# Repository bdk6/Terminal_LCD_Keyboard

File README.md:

# Terminal_LCD_Keyboard
 A generic keypad and lcd terminal.

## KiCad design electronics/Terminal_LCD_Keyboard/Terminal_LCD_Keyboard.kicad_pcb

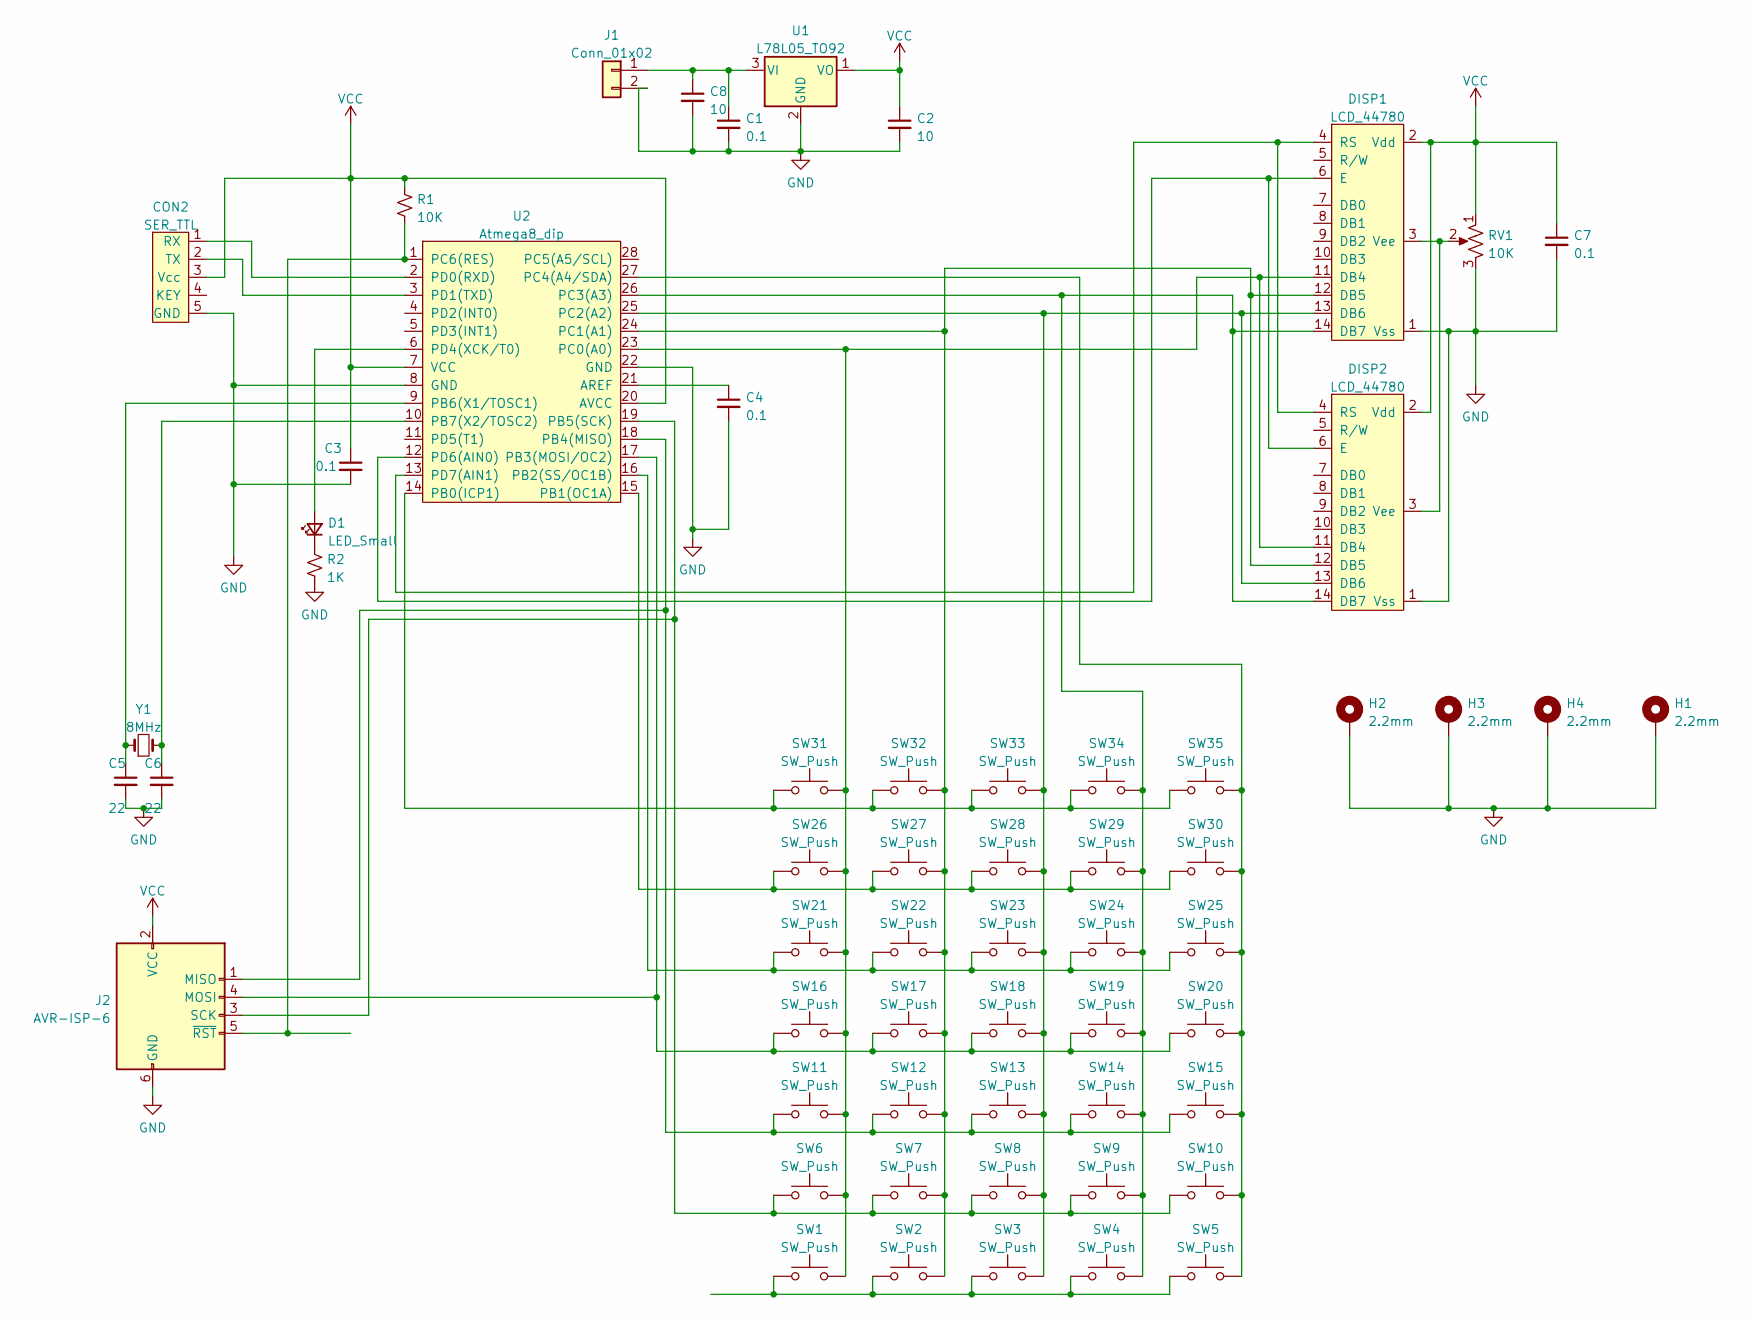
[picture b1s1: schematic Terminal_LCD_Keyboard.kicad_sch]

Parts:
C1: 0.1; C_Disc_D5.0mm_W2.5mm_P5.00mm
C2, C8: 10; CP_Radial_D6.3mm_P2.50mm
C3, C4, C7: 0.1; C_Disc_D6.0mm_W2.5mm_P5.00mm
C5, C6: 22; C_Disc_D6.0mm_W2.5mm_P5.00mm
CON2: SER_TTL; PinHeader_1x05_P2.54mm_Vertical
D1: LED_Small; D_0603_1608Metric_Pad1.05x0.95mm_HandSolder
DISP1: LCD_44780; PinHeader_1x14_P2.54mm_Vertical
DISP2: LCD_44780; PinHeader_1x16_P1.27mm_Vertical
H1, H2, H3, H4: 2.2mm; MountingHole_2.2mm_M2_DIN965_Pad
J1: Conn_01x02; PinHeader_1x02_P2.54mm_Vertical
J2: AVR-ISP-6; PinHeader_2x03_P2.54mm_Vertical
R1: 10K; R_Axial_DIN0207_L6.3mm_D2.5mm_P10.16mm_Horizontal
R2: 1K; D_0603_1608Metric_Pad1.05x0.95mm_HandSolder
RV1: 10K; Potentiometer_ACP_CA9-H5_Horizontal
SW1, SW2, SW3, SW4, SW5, SW6, SW7, SW8, SW9, SW10, SW11, SW12, SW13, SW14, SW15, SW16, SW17, SW18, SW19, SW20, SW21, SW22, SW23, SW24, SW25, SW26, SW27, SW28, SW29, SW30, SW31, SW32, SW33, SW34, SW35: SW_Push; SW_PUSH_6mm
U1: L78L05_TO92; TO-92_Inline
U2: Atmega8_dip; DIP-28_W7.62mm_Socket_LongPads
Y1: 8MHz; Crystal_HC49-U_Vertical

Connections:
GND: C1.2, C2.2, C3.2, C4.2, C5.2, C6.2, C7.2, C8.2, CON2.5 (GND), DISP1.1 (Vss), DISP2.1 (Vss), H1.1, H2.1, H3.1, H4.1, J1.2, J2.6 (GND), R2.2, RV1.3, U1.2 (GND), U2.8 (GND), U2.22 (GND)
unnamed: C1.1, C8.1, J1.1, U1.3 (VI)
unnamed: C4.1, U2.21 (AREF)
unnamed: C5.1, U2.9 (PB6(X1/TOSC1)), Y1.1
unnamed: C6.1, U2.10 (PB7(X2/TOSC2)), Y1.2
unnamed: CON2.1 (RX), U2.2 (PD0(RXD))
unnamed: CON2.2 (TX), U2.3 (PD1(TXD))
unnamed: D1.2 (A), U2.6 (PD4(XCK/T0))
unnamed: DISP1.3 (Vee), DISP2.3 (Vee), RV1.2
unnamed: DISP1.4 (RS), DISP2.4 (RS), U2.13 (PD7(AIN1))
unnamed: DISP1.6 (E), DISP2.6 (E), U2.12 (PD6(AIN0))
unnamed: DISP1.11 (DB4), DISP2.11 (DB4), SW1.2, SW6.2, SW11.2, SW16.2, SW21.2, SW26.2, SW31.2, U2.23 (PC0(A0))
unnamed: DISP1.12 (DB5), DISP2.12 (DB5), SW2.2, SW7.2, SW12.2, SW17.2, SW22.2, SW27.2, SW32.2, U2.24 (PC1(A1))
unnamed: DISP1.13 (DB6), DISP2.13 (DB6), SW3.2, SW8.2, SW13.2, SW18.2, SW23.2, SW28.2, SW33.2, U2.25 (PC2(A2))
unnamed: DISP1.14 (DB7), DISP2.14 (DB7), SW4.2, SW9.2, SW14.2, SW19.2, SW24.2, SW29.2, SW34.2, U2.26 (PC3(A3))
unnamed: J2.1 (MISO), SW11.1, SW12.1, SW13.1, SW14.1, SW15.1, U2.18 (PB4(MISO))
unnamed: J2.3 (SCK), SW6.1, SW7.1, SW8.1, SW9.1, SW10.1, U2.19 (PB5(SCK))
unnamed: J2.4 (MOSI), SW16.1, SW17.1, SW18.1, SW19.1, SW20.1, U2.17 (PB3(MOSI/OC2))
unnamed: J2.5 (~RST), R1.2, U2.1 (PC6(RES))
unnamed: D1.1 (K), R2.1
unnamed: SW1.1, SW2.1, SW3.1, SW4.1, SW5.1
unnamed: SW5.2, SW10.2, SW15.2, SW20.2, SW25.2, SW30.2, SW35.2, U2.27 (PC4(A4/SDA))
unnamed: SW21.1, SW22.1, SW23.1, SW24.1, SW25.1, U2.16 (PB2(SS/OC1B))
unnamed: SW26.1, SW27.1, SW28.1, SW29.1, SW30.1, U2.15 (PB1(OC1A))
unnamed: SW31.1, SW32.1, SW33.1, SW34.1, SW35.1, U2.14 (PB0(ICP1))
VCC: C2.1, C3.1, C7.1, CON2.3 (Vcc), DISP1.2 (Vdd), DISP2.2 (Vdd), J2.2 (VCC), R1.1, RV1.1, U1.1 (VO), U2.7 (VCC), U2.20 (AVCC)

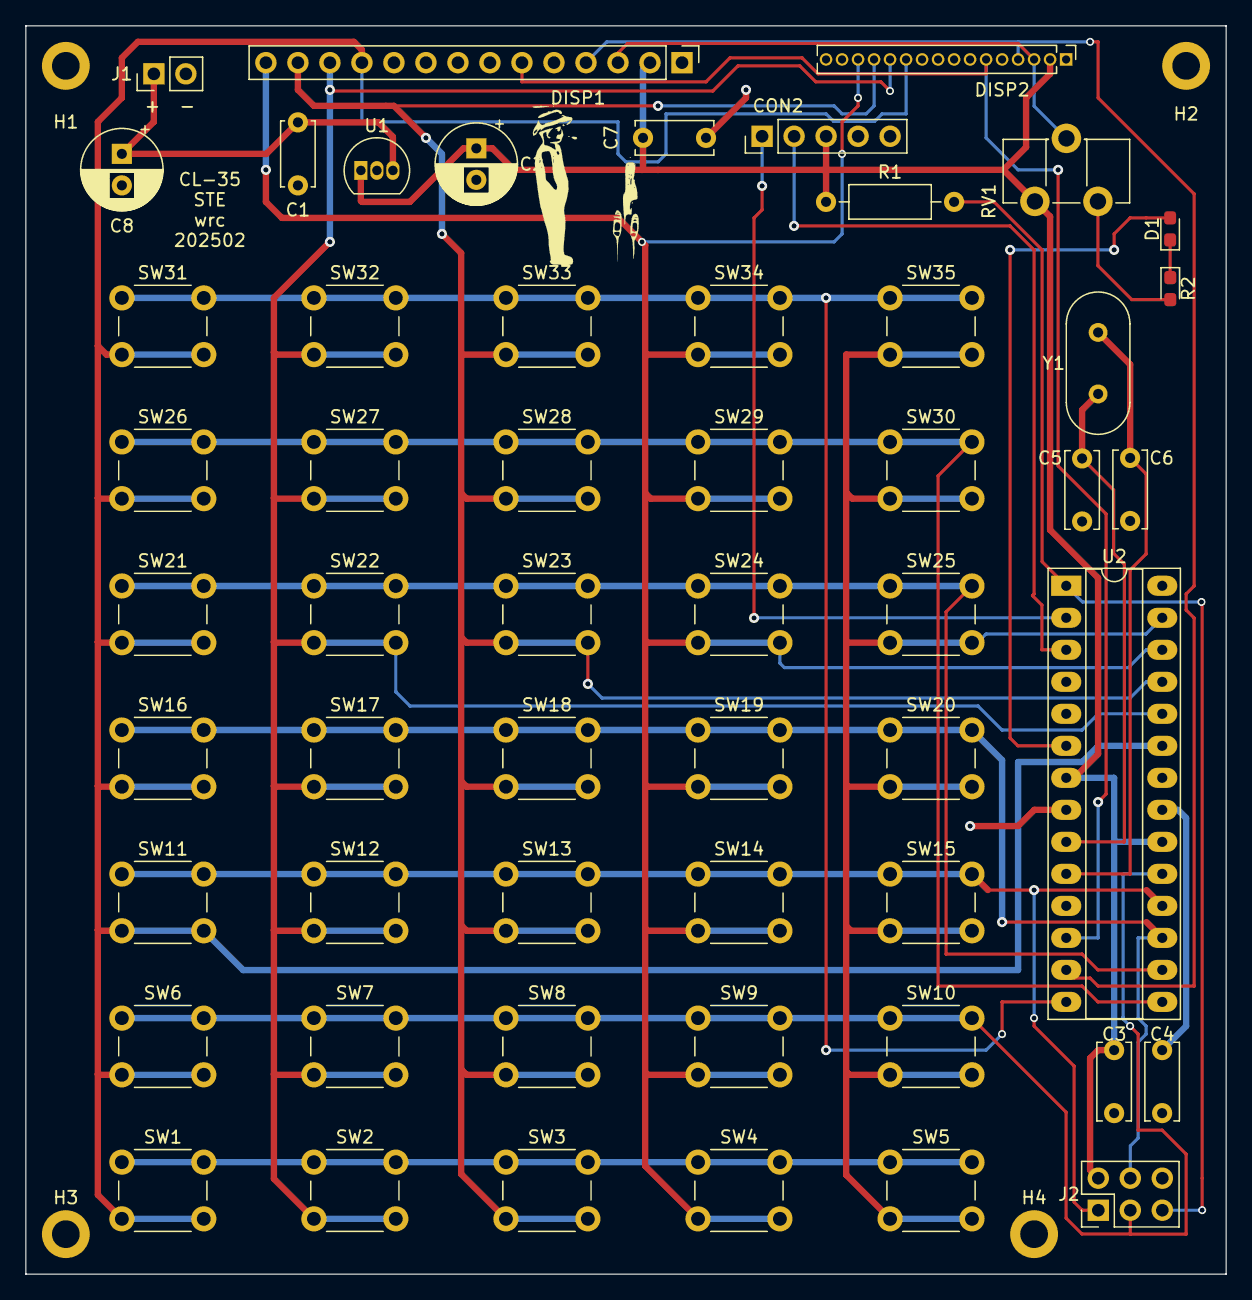
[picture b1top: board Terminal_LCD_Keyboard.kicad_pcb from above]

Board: 2 copper layers, 95.2 x 99.1 mm, 59 parts (0 on the bottom side), 26 nets.

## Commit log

2025-02-26 Finished pcb layout.
2025-02-26 Added schematic pdf and some unknown changes to pcb
2025-03-21 Cleanup from project directory
